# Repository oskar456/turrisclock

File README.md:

TurrisClock
===========

Driving clock movement from the Turris Router.

See the [project page](http://oskar456.github.io/turrisclock/) for more informations.

This is a simple set of python scripts for driving hardware clock connected to GPIO pins of a computer
(like [Turris router](https://www.turris.cz/)). Two GPIO pins are used. First GPIO pin named CLK enables/disables
powering the step motor (0 = powered off, 1 = powered on). Second GPIO pin is used to control the polarity of
current flowing through the motor. In case the clock movement appears to be 1 second slow, you should
either swap wires connecting the step motor or activate polarity inversion in Clock class.

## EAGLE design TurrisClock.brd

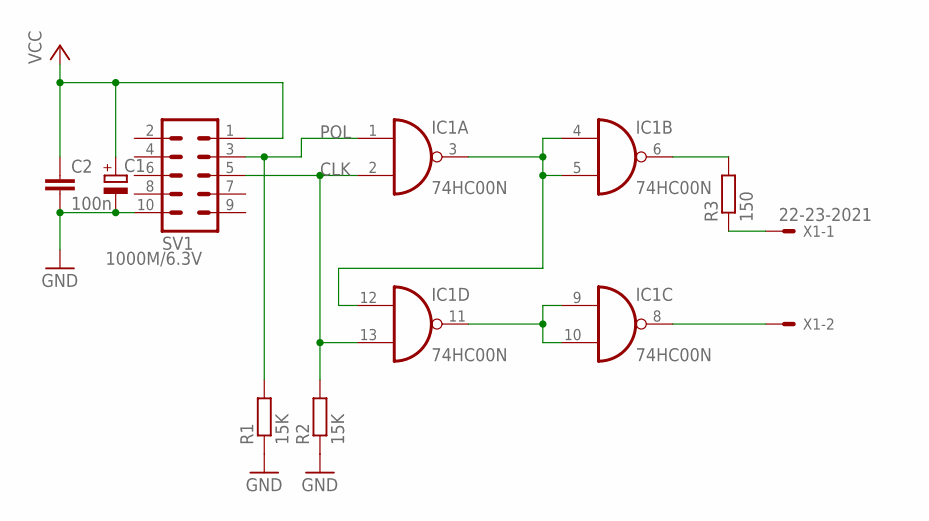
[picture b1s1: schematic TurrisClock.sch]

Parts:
C1: 1000M/6.3V; E5-8,5
C2: 100n; C050-024X044
IC1: 74HC00N; DIL14
R1, R2: 15K; 0204/7
R3: 150; 0204/7
SV1: ML10
X1: 22-23-2021

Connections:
CLK: IC1.2 (I1), IC1.13 (I1), R2.2, SV1.5
GND: C1.-, C2.2, IC1.7 (GND), R1.1, R2.1, SV1.10
unnamed: IC1.3 (O), IC1.4 (I0), IC1.5 (I1), IC1.12 (I0)
unnamed: IC1.9 (I0), IC1.10 (I1), IC1.11 (O)
unnamed: IC1.6 (O), R3.2
unnamed: IC1.8 (O), X1.2
unnamed: R3.1, X1.1
POL: IC1.1 (I0), R1.2, SV1.3
VCC: C1.+, C2.1, IC1.14 (VCC), SV1.1

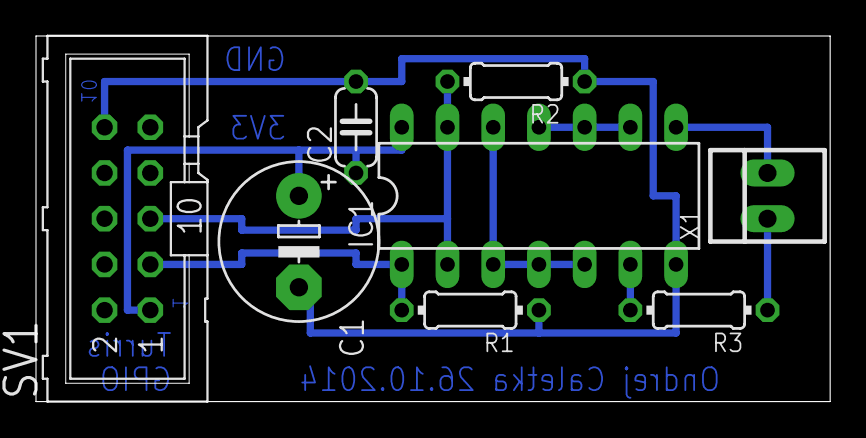
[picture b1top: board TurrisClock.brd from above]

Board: 2 copper layers, 44.1 x 20.3 mm, 8 parts (0 on the bottom side), 9 nets.

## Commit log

2014-10-22 Added wait function when clock is too fast
    In case the movement is too fast, it's sometimes better to wait
    instead of stepping all round the clock. To calm users, comfort
    step is inserted every 10 seconds while waiting (which makes the
    calculation wait time calculation recursive :) )
2014-10-22 Initial commit of messy but working prototype
2014-10-22 Reimplement timetowait using sum of infinite sequence
2014-10-22 Major code refactoring, (hopefully) without breaking anything
2014-10-24 Quick and dirty hack to use MSP430 Launchpad as a GPIO expander
2014-10-25 New software for MSP430, using singleton for GPIO
2014-10-25 Refactor comfort step
2014-10-25 Add step support
2014-10-26 Refactor clock control with unified waiting/stepping
2014-10-26 Factor common functions out of turrisclock main
2014-10-26 New simple executable goto.py <hh:mm:ss>
2014-10-26 Exchange GPIO pins according to new HW design
2014-10-26 Account for exchanging GPIO
2014-10-26 Factor common functions out of turrisclock main
    Conflicts:
    clock.py
    turrisclock.py
2014-10-27 Fix same minor problems with timekeeping logic
    Now even weird steprates like 7 works correctly.
    Precise syncing with long intervals still does not work well.
2014-10-27 Fix same minor problems with timekeeping logic
    Now even weird steprates like 7 works correctly.
    Precise syncing with long intervals still does not work well.
    Conflicts:
    clock.py
2014-11-20 Add readme
2014-11-20 Create gh-pages branch via GitHub
2014-11-21 Some minor fixes of clock.py
2014-11-21 Refactor main loop to implement stepping properly
2014-11-23 Add some images
2015-05-06 Add more pictures
2016-04-14 Change GPIO pin numbers for the new kernel
2016-04-14 Store hand position in the NVRAM of RTC
    This is additional storage of the hand position in the RTC so it is
    backed up by battery and the number of rewrites is unlimited.
    The hand position is stored with every step and reloaded on every start.
2016-04-14 Timing constants adjustment
2016-04-15 Add new option --require-nvram
    Useful for running from init script so the clock don't sync to a random
    state in case of a power outage and the RTC battery failure
2018-01-18 Use native python Turris GPIO library instead of sysfs
2018-01-18 Refactored test code
2018-01-18 Add init script
2018-01-18 Python 3 compatibility
2018-01-18 Flake8 fixes
2018-01-18 Update NVRAM store path
2018-01-18 Magic should be binstring
2018-01-18 Set Python 3 as default shebang
